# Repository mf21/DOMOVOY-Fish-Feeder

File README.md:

# DOMOVOY-Fish-Feeder
Smart Fish Feeder is a part of DOMOVOY home automation project

https://www.mf21.ru - russian site,

https://www.diyorbuy.tech - english site

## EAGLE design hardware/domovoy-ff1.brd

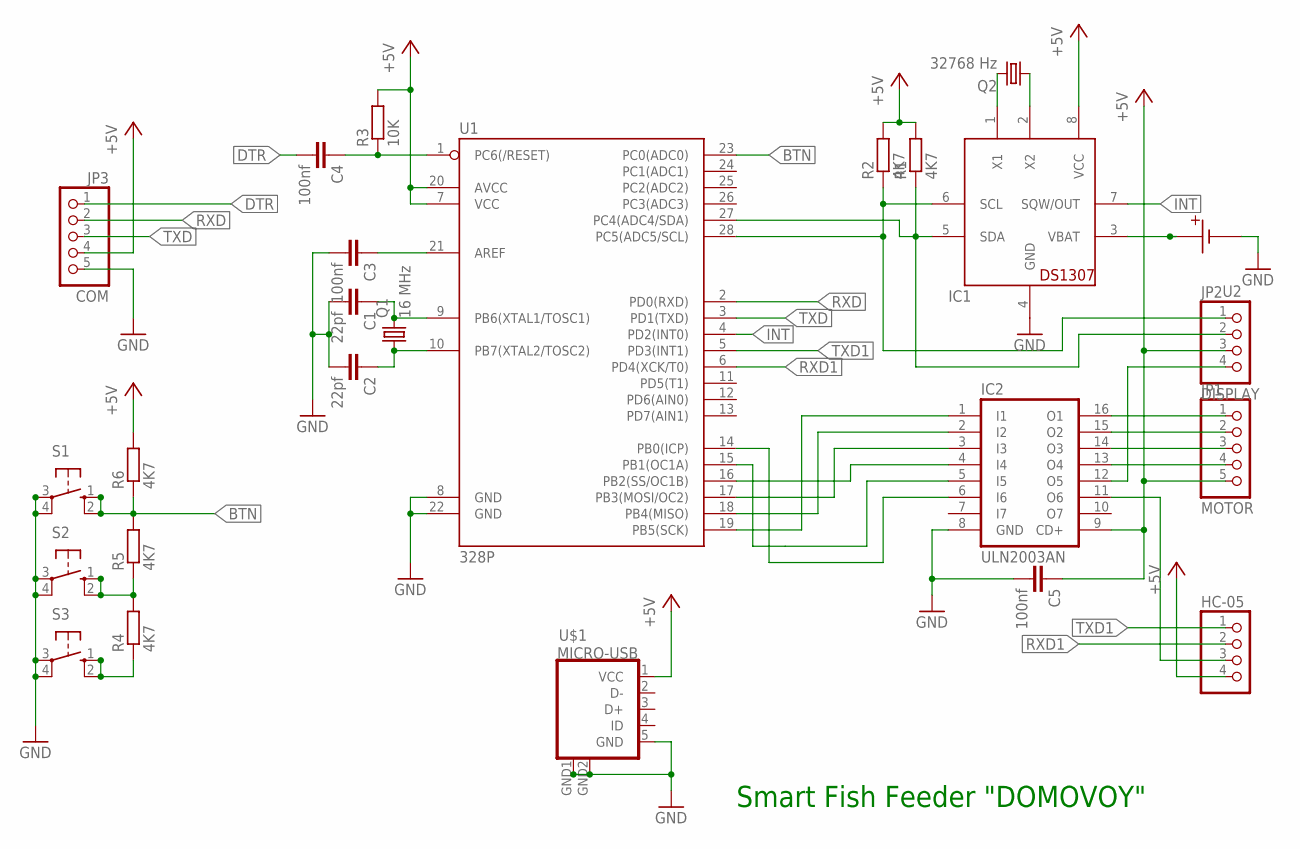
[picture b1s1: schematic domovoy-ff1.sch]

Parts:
C1, C2: 22pf; C1206
C3, C4, C5: 100nf; C1206
HC-05: PINHD-1X4; 1X04
IC1: DS1307; DIL08
IC2: ULN2003AN; DIL16
JP1: MOTOR; 1X05
JP2: DISPLAY; 1X04
JP3: COM; 1X05
Q1: 16 MHz; HC49/S
Q2: 32768 Hz; TC38H
R1, R2, R4, R5, R6: 4K7; R1206
R3: 10K; R1206
S1, S2, S3: 10-XX; B3F-10XX
U1: 328P; DIP28
U2: CR2032-HOLDERSTANDARD; DIP
U$1: MICRO-USB

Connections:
+5V: C5.1, HC-05.4, IC1.8 (VCC), IC2.9 (CD+), JP1.5, JP2.3, JP3.4, R1.2, R2.2, R3.2, R6.2, U1.7 (VCC), U1.20 (AVCC), U$1.1 (VCC)
BTN: R5.2, R6.1, S1.1 (S), S1.2 (S1), U1.23 (PC0(ADC0))
DTR: C4.2, JP3.1
GND: C1.2, C2.2, C3.2, C5.2, IC1.4 (GND), IC2.8 (GND), JP3.5, S1.3, S1.4 (P1), S2.3, S2.4 (P1), S3.3, S3.4 (P1), U1.8 (GND), U1.22 (GND), U2.GND, U$1.5 (GND), U$1.GND1 (GND), U$1.GND2 (GND)
INT: IC1.7 (SQW/OUT), U1.4 (PD2(INT0))
unnamed: C1.1, Q1.2, U1.9 (PB6(XTAL1/TOSC1))
unnamed: C2.1, Q1.1, U1.10 (PB7(XTAL2/TOSC2))
unnamed: IC2.1 (I1), U1.19 (PB5(SCK))
unnamed: IC2.2 (I2), U1.18 (PB4(MISO))
unnamed: IC2.3 (I3), U1.17 (PB3(MOSI/OC2))
unnamed: IC2.4 (I4), U1.16 (PB2(SS/OC1B))
unnamed: C4.1, R3.1, U1.1 (PC6(/RESET))
unnamed: IC1.1 (X1), Q2.2
unnamed: IC1.2 (X2), Q2.1
unnamed: IC1.6 (SCL), JP2.1, R2.1, U1.28 (PC5(ADC5/SCL))
unnamed: IC1.5 (SDA), JP2.2, R1.1, U1.27 (PC4(ADC4/SDA))
unnamed: C3.1, U1.21 (AREF)
unnamed: IC2.16 (O1), JP1.1
unnamed: IC2.15 (O2), JP1.2
unnamed: IC2.14 (O3), JP1.3
unnamed: IC2.13 (O4), JP1.4
unnamed: IC1.3 (VBAT), U2.POWER
unnamed: IC2.12 (O5), JP2.4
unnamed: R4.2, R5.1, S2.1 (S), S2.2 (S1)
unnamed: R4.1, S3.1 (S), S3.2 (S1)
unnamed: IC2.5 (I5), U1.15 (PB1(OC1A))
unnamed: HC-05.3, IC2.11 (O6)
unnamed: IC2.6 (I6), U1.14 (PB0(ICP))
RXD: JP3.2, U1.2 (PD0(RXD))
RXD1: HC-05.2, U1.6 (PD4(XCK/T0))
TXD: JP3.3, U1.3 (PD1(TXD))
TXD1: HC-05.1, U1.5 (PD3(INT1))

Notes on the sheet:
Smart Fish Feeder "DOMOVOY"

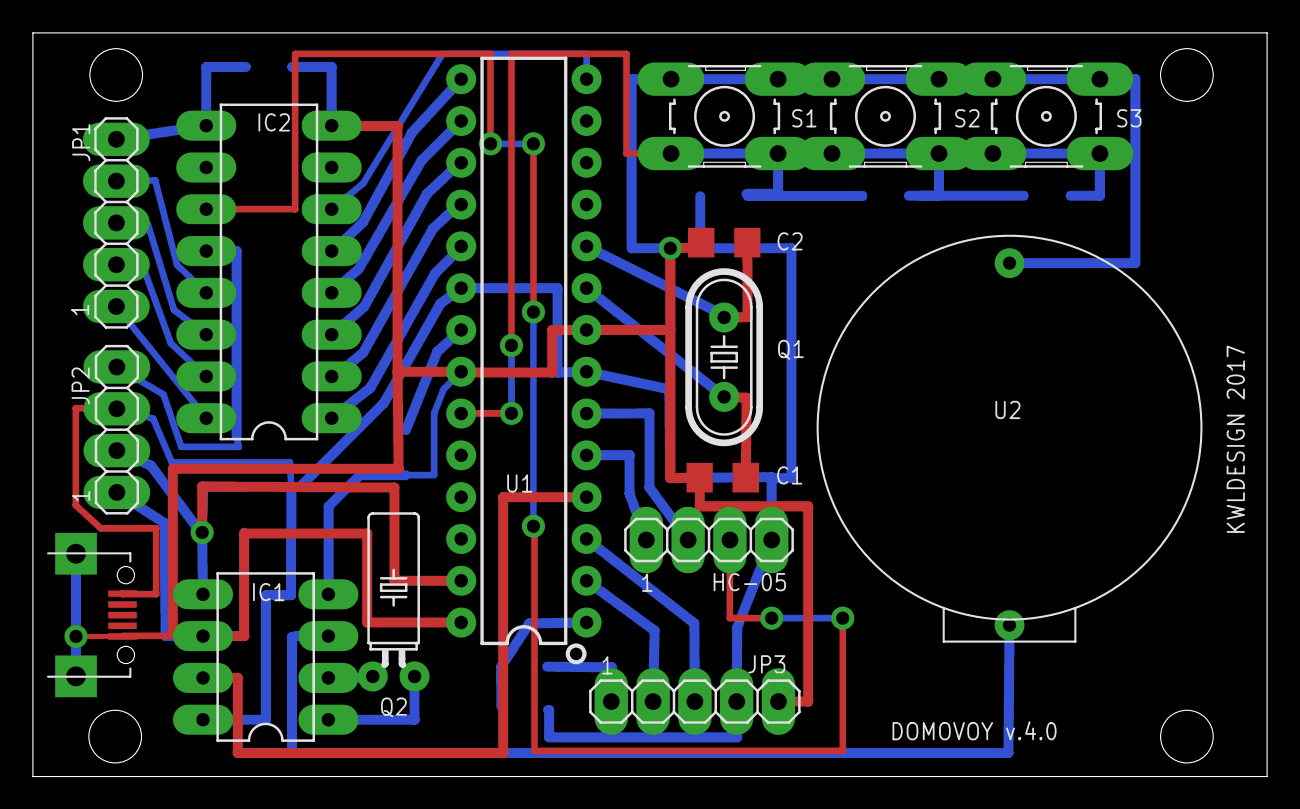
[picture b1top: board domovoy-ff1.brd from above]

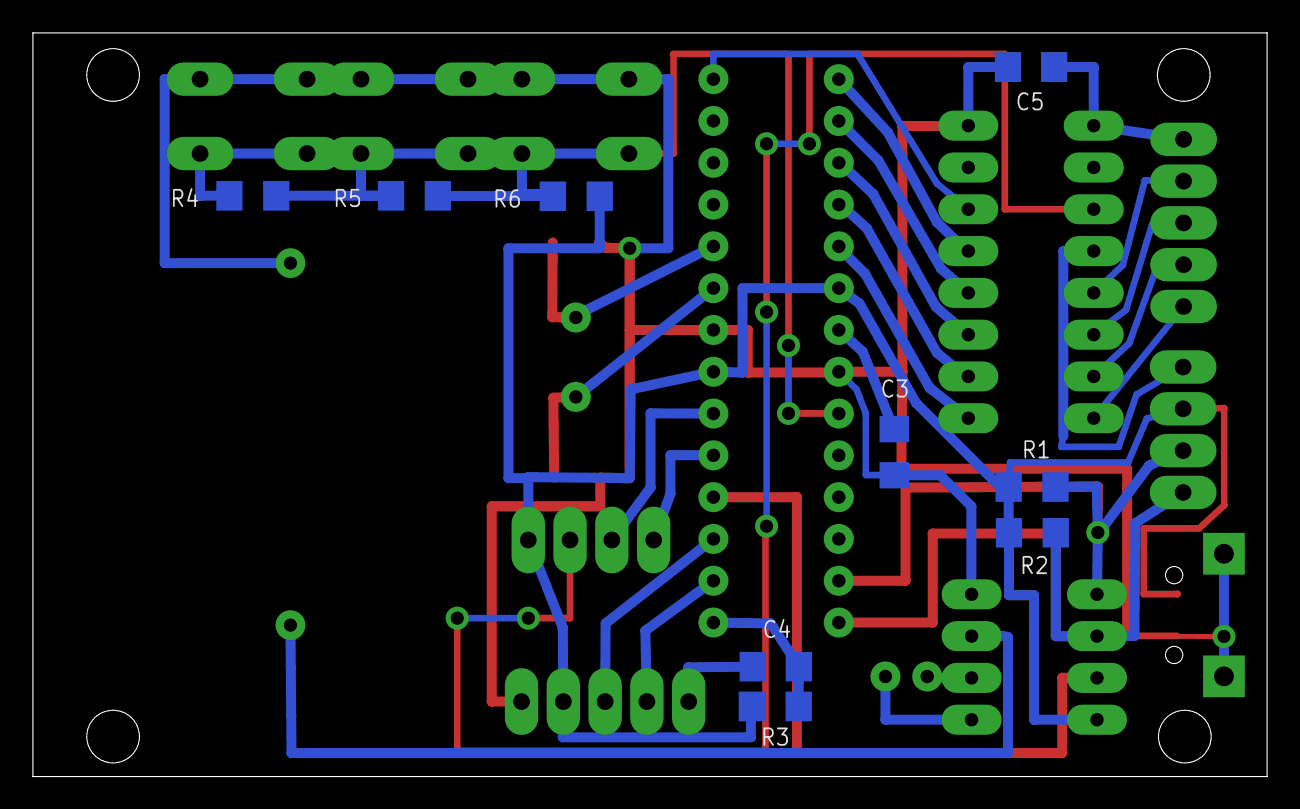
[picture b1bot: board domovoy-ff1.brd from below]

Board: 2 copper layers, 75.0 x 45.2 mm, 25 parts (9 on the bottom side), 32 nets.

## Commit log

2018-02-25 Change readme
2018-04-03 Instruction of assembly PCB board added
2018-04-03 The file name has been changed
2018-04-13 The code is separated into enlish and russian languages
2018-04-14 PCB assembly document added
2018-04-18 Bluetooth protocol documentation added
2018-04-23 Update firmware.ino
    Traslation bug fixed
2018-04-23 Translation bug fixed
2018-08-26 File added

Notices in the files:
parts and their libraries:
SparkFun-IC-Microcontroller: Licensing: Creative Commons ShareAlike 4.0 International - https://creativecommons.org/licenses/by-sa/4.0
